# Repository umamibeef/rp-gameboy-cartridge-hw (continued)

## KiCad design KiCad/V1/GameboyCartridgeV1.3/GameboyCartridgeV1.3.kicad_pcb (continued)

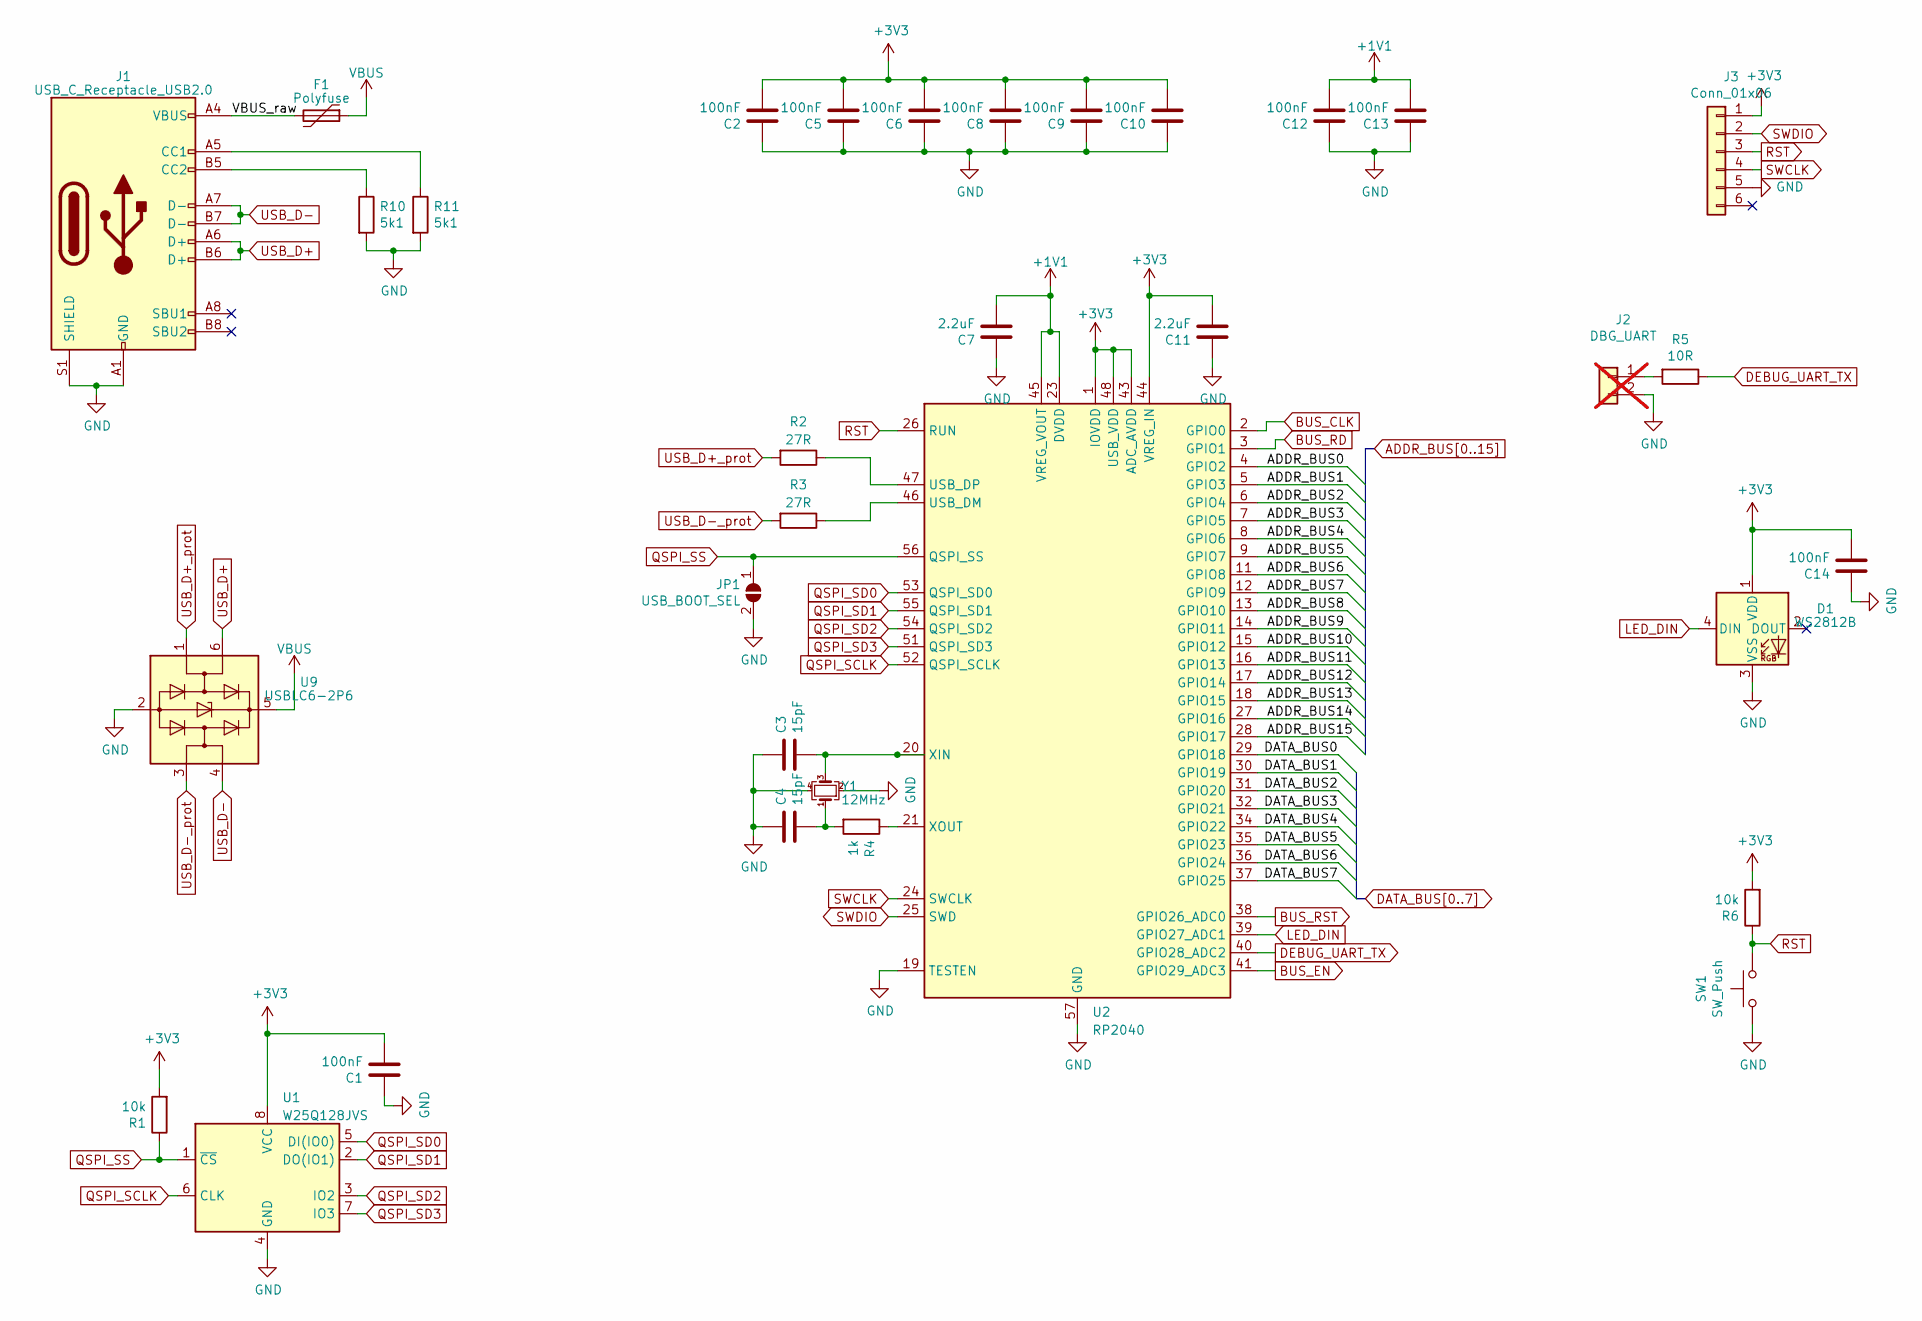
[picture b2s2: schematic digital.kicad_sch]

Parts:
C1, C14: 100nF; C_0603_1608Metric_Pad1.08x0.95mm_HandSolder
C2, C5, C6, C8, C9, C10, C12, C13: 100nF; C_0402_1005Metric_Pad0.74x0.62mm_HandSolder
C3, C4: 15pF; C_0603_1608Metric_Pad1.08x0.95mm_HandSolder; LCSC C1644
C7, C11: 2.2uF; C_0603_1608Metric_Pad1.08x0.95mm_HandSolder
D1: WS2812B; LED_WS2812B_PLCC4_5.0x5.0mm_P3.2mm; LCSC C2761795
F1: Polyfuse; Fuse_1206_3216Metric; LCSC C6964264
J1: USB_C_Receptacle_USB2.0; USB_C_Receptacle_GCT_USB4105-xx-A_16P_TopMnt_Horizontal; LCSC C2927037
J2: DBG_UART; PinHeader_1x02_P2.54mm_Horizontal; not fitted
J3: Conn_01x06; Tag-Connect_TC2030-IDC-FP_2x03_P1.27mm_Vertical
JP1: USB_BOOT_SEL; SolderJumper-2_P1.3mm_Open_RoundedPad1.0x1.5mm
R1, R6: 10k; R_0603_1608Metric_Pad0.98x0.95mm_HandSolder
R2, R3: 27R; R_0603_1608Metric_Pad0.98x0.95mm_HandSolder
R4: 1k; R_0603_1608Metric_Pad0.98x0.95mm_HandSolder
R5: 10R; R_0603_1608Metric_Pad0.98x0.95mm_HandSolder
R10, R11: 5k1; R_0603_1608Metric_Pad0.98x0.95mm_HandSolder
SW1: SW_Push; SW_SPST_TL3342; LCSC C2886898
U1: W25Q128JVS; SOIC-8_5.23x5.23mm_P1.27mm; LCSC C97521
U2: RP2040; QFN-56-1EP_7x7mm_P0.4mm_EP3.2x3.2mm; LCSC C2040
U9: USBLC6-2P6; SOT-666; LCSC C15999
Y1: 12MHz; Crystal_SMD_TXC_7M-4Pin_3.2x2.5mm; LCSC C668845

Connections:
+1V1: C7.2, C12.2, C13.2, U2.23 (DVDD), U2.45 (VREG_VOUT), U2.50 (DVDD)
+3V3: C1.2, C2.2, C5.2, C6.2, C8.2, C9.2, C10.2, C11.2, C14.2, D1.1 (VDD), J3.1, R1.2, R6.2, U1.8 (VCC), U2.1 (IOVDD), U2.10 (IOVDD), U2.22 (IOVDD), U2.33 (IOVDD), U2.42 (IOVDD), U2.43 (ADC_AVDD), U2.44 (VREG_IN), U2.48 (USB_VDD), U2.49 (IOVDD); also elsewhere on the board
/Digital/VBUS_raw: F1.2, J1.A4 (VBUS), J1.A9 (VBUS), J1.B4 (VBUS), J1.B9 (VBUS)
ADDR_BUS0: U2.4 (GPIO2); also elsewhere on the board
ADDR_BUS1: U2.5 (GPIO3); also elsewhere on the board
ADDR_BUS2: U2.6 (GPIO4); also elsewhere on the board
ADDR_BUS3: U2.7 (GPIO5); also elsewhere on the board
ADDR_BUS4: U2.8 (GPIO6); also elsewhere on the board
ADDR_BUS5: U2.9 (GPIO7); also elsewhere on the board
ADDR_BUS6: U2.11 (GPIO8); also elsewhere on the board
ADDR_BUS7: U2.12 (GPIO9); also elsewhere on the board
ADDR_BUS8: U2.13 (GPIO10); also elsewhere on the board
ADDR_BUS9: U2.14 (GPIO11); also elsewhere on the board
ADDR_BUS10: U2.15 (GPIO12); also elsewhere on the board
ADDR_BUS11: U2.16 (GPIO13); also elsewhere on the board
ADDR_BUS12: U2.17 (GPIO14); also elsewhere on the board
ADDR_BUS13: U2.18 (GPIO15); also elsewhere on the board
ADDR_BUS14: U2.27 (GPIO16); also elsewhere on the board
ADDR_BUS15: U2.28 (GPIO17); also elsewhere on the board
BUS_CLK: U2.2 (GPIO0); also elsewhere on the board
BUS_EN: U2.41 (GPIO29_ADC3); also elsewhere on the board
BUS_RD: U2.3 (GPIO1); also elsewhere on the board
BUS_RST: U2.38 (GPIO26_ADC0); also elsewhere on the board
DATA_BUS0: U2.29 (GPIO18); also elsewhere on the board
DATA_BUS1: U2.30 (GPIO19); also elsewhere on the board
DATA_BUS2: U2.31 (GPIO20); also elsewhere on the board
DATA_BUS3: U2.32 (GPIO21); also elsewhere on the board
DATA_BUS4: U2.34 (GPIO22); also elsewhere on the board
DATA_BUS5: U2.35 (GPIO23); also elsewhere on the board
DATA_BUS6: U2.36 (GPIO24); also elsewhere on the board
DATA_BUS7: U2.37 (GPIO25); also elsewhere on the board
DEBUG_UART_TX: R5.1, U2.40 (GPIO28_ADC2)
GND: C1.1, C2.1, C3.1, C4.1, C5.1, C6.1, C7.1, C8.1, C9.1, C10.1, C11.1, C12.1, C13.1, C14.1, D1.3 (VSS), J1.A1 (GND), J1.A12 (GND), J1.B1 (GND), J1.B12 (GND), J1.S1 (SHIELD), J2.2, J3.5, JP1.2 (B), R10.2, R11.2, SW1.2, U1.4 (GND), U2.19 (TESTEN), U2.57 (GND), U9.2 (GND), Y1.2, Y1.4; also elsewhere on the board
LED_DIN: D1.4 (DIN), U2.39 (GPIO27_ADC1)
unnamed: C4.2, R4.2, Y1.1
unnamed: J1.A5 (CC1), R11.1
unnamed: J1.B5 (CC2), R10.1
unnamed: J2.1, R5.2
unnamed: R3.1, U2.46 (USB_DM)
unnamed: R2.1, U2.47 (USB_DP)
unnamed: C3.2, U2.20 (XIN), Y1.3
unnamed: R4.1, U2.21 (XOUT)
QSPI_SCLK: U1.6 (CLK), U2.52 (QSPI_SCLK)
QSPI_SD0: U1.5 (DI(IO0)), U2.53 (QSPI_SD0)
QSPI_SD1: U1.2 (DO(IO1)), U2.55 (QSPI_SD1)
QSPI_SD2: U1.3 (IO2), U2.54 (QSPI_SD2)
QSPI_SD3: U1.7 (IO3), U2.51 (QSPI_SD3)
QSPI_SS: JP1.1 (A), R1.1, U1.1 (~CS), U2.56 (QSPI_SS)
RST: J3.3, R6.1, SW1.1, U2.26 (RUN)
SWCLK: J3.4, U2.24 (SWCLK)
SWDIO: J3.2, U2.25 (SWD)
USB_D+: J1.A6 (D+), J1.B6 (D+), U9.6 (I/O1)
USB_D+_prot: R2.2, U9.1 (I/O1)
USB_D-: J1.A7 (D-), J1.B7 (D-), U9.4 (I/O2)
USB_D-_prot: R3.2, U9.3 (I/O2)
VBUS: F1.1, U9.5 (VBUS); also elsewhere on the board

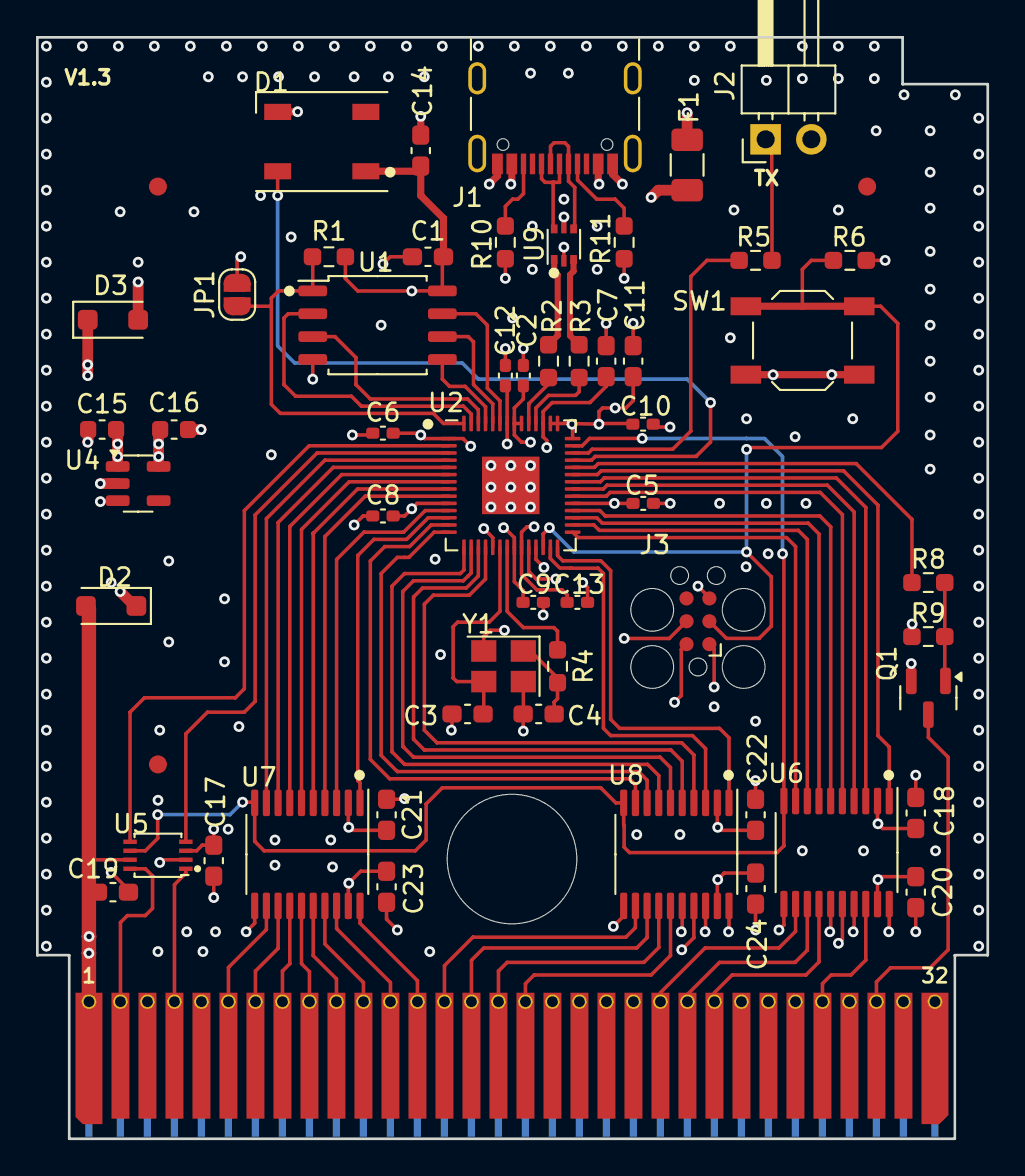
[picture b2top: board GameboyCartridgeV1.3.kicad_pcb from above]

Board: 4 copper layers, 52.8 x 61.2 mm, 57 parts (0 on the bottom side), 86 nets.

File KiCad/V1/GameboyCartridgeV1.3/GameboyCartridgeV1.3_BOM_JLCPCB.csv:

Comment,Designator,Footprint,LCSC Part Number
"100nF","C1,C14,C17,C18,C19,C20,C21,C22,C23,C24","Capacitor_SMD:C_0603_1608Metric_Pad1.08x0.95mm_HandSolder","C14663"
"100nF","C2,C5,C6,C8,C9,C10,C12,C13","Capacitor_SMD:C_0402_1005Metric_Pad0.74x0.62mm_HandSolder","C1525"
"15pF","C3,C4","Capacitor_SMD:C_0603_1608Metric_Pad1.08x0.95mm_HandSolder","C1644"
"2.2uF","C7,C11","Capacitor_SMD:C_0603_1608Metric_Pad1.08x0.95mm_HandSolder",""
"1uF","C15,C16","Capacitor_SMD:C_0603_1608Metric",""
"WS2812B","D1","LED_SMD:LED_WS2812B_PLCC4_5.0x5.0mm_P3.2mm","C2761795"
"D_Schottky","D2,D3","Diode_SMD:D_SOD-123F","C669022"
"Polyfuse","F1","Fuse:Fuse_1206_3216Metric","C6964264"
"USB_C_Receptacle_USB2.0","J1","Connector_USB:USB_C_Receptacle_GCT_USB4105-xx-A_16P_TopMnt_Horizontal","C2927037"
"CJ2302","Q1","Package_TO_SOT_SMD:SOT-23","C8548"
"10k","R1,R6,R9","Resistor_SMD:R_0603_1608Metric_Pad0.98x0.95mm_HandSolder",""
"27R","R2,R3","Resistor_SMD:R_0603_1608Metric_Pad0.98x0.95mm_HandSolder",""
"1k","R4,R8","Resistor_SMD:R_0603_1608Metric_Pad0.98x0.95mm_HandSolder",""
"10R","R5","Resistor_SMD:R_0603_1608Metric_Pad0.98x0.95mm_HandSolder",""
"5k1","R10,R11","Resistor_SMD:R_0603_1608Metric_Pad0.98x0.95mm_HandSolder",""
"SW_Push","SW1","Button_Switch_SMD:SW_SPST_TL3342","C2886898"
"W25Q128JVS","U1","Package_SO:SOIC-8_5.23x5.23mm_P1.27mm","C97521"
"RP2040","U2","Package_DFN_QFN:QFN-56-1EP_7x7mm_P0.4mm_EP3.2x3.2mm","C2040"
"AP2112K-3.3","U4","Package_TO_SOT_SMD:SOT-23-5","C51118"
"TXB0102DCU","U5","Package_SO:VSSOP-8_2.4x2.1mm_P0.5mm","C60709"
"TXB0108PW","U6,U7,U8","Package_SO:TSSOP-20_4.4x6.5mm_P0.65mm","C53406"
"USBLC6-2P6","U9","Package_TO_SOT_SMD:SOT-666","C15999"
"12MHz","Y1","Crystal:Crystal_SMD_TXC_7M-4Pin_3.2x2.5mm","C668845"

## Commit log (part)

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2025-11-29 Publish of V1.3
